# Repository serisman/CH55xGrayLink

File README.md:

Not a really meaning full PR but just a message.

This brought me back the memory of using a second hand official cable to load games onto the 83+ 16 years ago. And I'm still using the same calculater for basic calculation today.

Very happy to see you combined ch55xduino and 83+. Good job!

# CH55xGrayLink
A sketch for CH551/CH552 based Arduinos (using [Ch55xduino](https://github.com/DeqingSun/ch55xduino)) that makes it possible to connect a Texas Instruments calculator to a computer using USB.

## Introduction
This sketch allows a computer to connect to and transfer data to/from a TI graphing calculator over USB.
It is a port of the *serial2ti83* Arduino sketch for Arduino Nano/Uno found [here](https://github.com/MTres19/serial2ti83).
In order to use it, compile and upload `CH55xGrayLink.ino` to a CH551 or CH552 [Ch55xduino](https://github.com/DeqingSun/ch55xduino) board using the Arduino IDE.

```
Sketch uses 4254 bytes (41%) of program storage space. Maximum is 10240 bytes.
Global variables use 59 bytes (16%) of dynamic memory, leaving 305 bytes for local variables. Maximum is 364 bytes.
```

## Wiring
Connect the following pins to the 2.5mm port located at the bottom of the TI calculator according to the following table:

| 2.5mm port    | CH55x         | 
|:-------------:|:-------------:|
| tip           | P1.4          |
| ring          | P1.7          |
| sleeve        | GND           |

## Transfer Speed
Max reported transfer speed seems to be about 3.2 KB/s based on testing done to date (TI-83 Plus).

## Arduino Settings
First, install Ch55xduino according to the instruction found here: https://github.com/DeqingSun/ch55xduino#installation

Then, select the CH551 Board (or CH552 Board) and adjust the other settings to match below.

Adjust *Port* as needed.  May need to use Device Manager to force the port to COM1-4 for TI programs to actually see it.

## Schematic

## PCB
Designed to fit within a standard USB-A male port housing.

Gerbers: `pcb/output/gerber.zip`

PCBs available from: [OSHPARK](https://oshpark.com/shared_projects/HASfmay6)

## Finished Cable
Note: This is picturing an older PCB (from a different project), but the optimized PCB available above is basically the same thing.

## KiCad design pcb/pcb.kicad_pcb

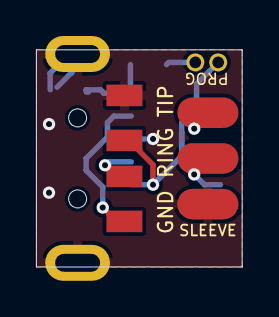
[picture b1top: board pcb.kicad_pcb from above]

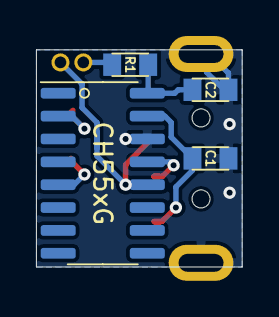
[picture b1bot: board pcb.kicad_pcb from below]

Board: 2 copper layers, 11.4 x 12.1 mm, 7 parts (5 on the bottom side), 8 nets.

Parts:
C1, C2: 100n; C_0805
J1: USB_A; USB_A_Horizontal_C319178
J2: TRS; PinHeader_1x03_P2.54mm_Horizontal
JP1: PROG; Jumper_P1.27mm
R1: 12k; R_0805
U1: CH55xG; SOIC-16_3.9x9.9mm_P1.27mm

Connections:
+3V3: C2.1, R1.2, U1.16
+5V: C1.1, J1.1, U1.15
/RING: J2.2, U1.5
/TIP: J2.3, U1.2
/UD+: J1.3, JP1.2, U1.12
/UD-: J1.2, U1.13
GND: C1.2, C2.2, J1.4, J1.5, J2.1, U1.14
unnamed: JP1.1, R1.1

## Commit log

2021-10-30 Ported to Ch55xduino
2021-10-30 Add missing image
2021-10-31 Add Schematic, PCB, and pictures of finished cable
2021-10-31 Clarify README.md
2021-10-31 Add sketch size
2021-10-31 Speed increase (at expense of timeout duration accuracy)
2021-12-09 Just a message
